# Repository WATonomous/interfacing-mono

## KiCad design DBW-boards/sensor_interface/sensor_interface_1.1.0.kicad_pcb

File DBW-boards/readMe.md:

# DBW Boards
- This folder contaisn schematics, pcb layouts, as well as component lists + where to order for the DBW boards for Watonomous's VP division.
- There are 4 boards to be assembled/fabricated off of these. 
##Boards
- Control (Brake)
- Can Gateway
- 2 Sensor boards, one for throttle and one for steering

### Each board is a Kicad project, simply download this repo and open them in Kicad.

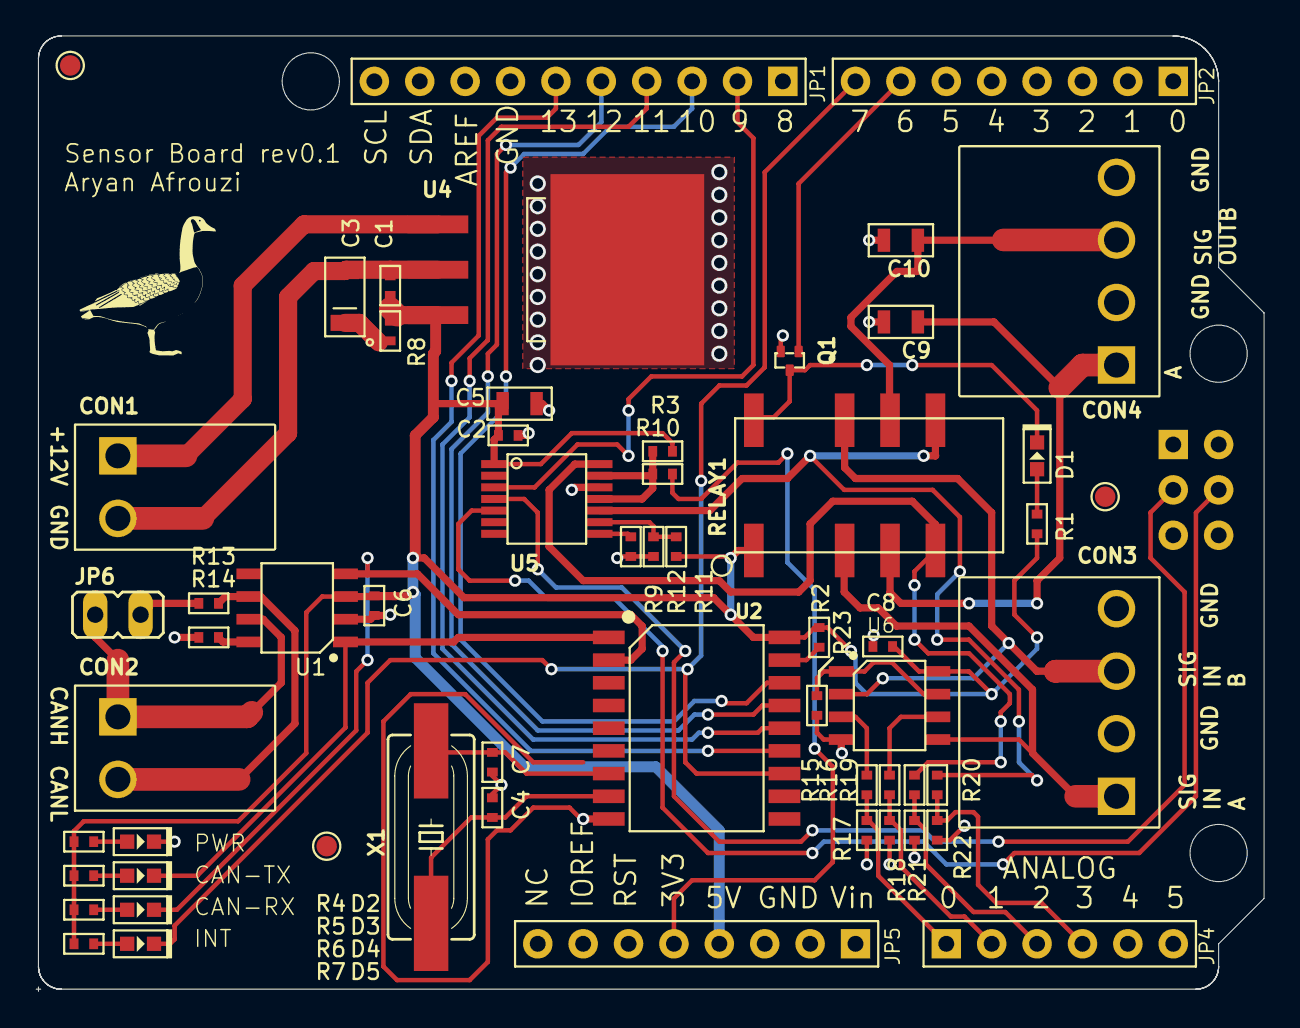
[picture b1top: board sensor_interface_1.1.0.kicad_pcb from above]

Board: 2 copper layers, 68.6 x 53.3 mm, 60 parts (0 on the bottom side), 45 nets.

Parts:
C1, C2, C6, C8: .1u; C0402
C3: 33u; CP1206
C4, C7: 22p; C0402
C5, C9, C10: 10u; C0805
CON1, CON2: CON23.5MM; PHOENIX_2_45
CON3, CON4: PHOENIX_4_45
D1, D4: Red; LED0603
D2, D3: Green; LED0603
D5: Blue; LED0603
JP1: ARDUINO_JP1
JP2: ARDUINO_JP2
JP3: ARDUINO_JP3
JP4: ARDUINO_JP4
JP5: ARDUINO_JP5
JP6: JP1
Q1: RE1C002UN; EMT3F
R1, R4, R5, R6, R7: 1k; R0402
R2, R9, R11, R17, R18, R23: 10k; R0402
R3, R15, R16, R19, R20: 0; R0402
R8: .3; R0402
R10, R12, R21, R22: DNP; R0402
R13: 120; R0402
R14: 47k; R0402
RELAY1: RELAY_DPDT; KEMET_EE2
TP1, TP2, TP3: TP_4545
U1: MCP2551; SOIC8-6.0
U2: MCP2515; SOIC18
U4: TL750M; TO-263
U5: MCP4922T; TSSOP-14
U6: SN74CBT3306CD; SOIC-8
U$1: POLYSYNC_STEERING_BOT
X1: 16MHz; HC49UP

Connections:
+3V3: JP5.22, R10.P$1
+5V: C1.P$1, C2.P$1, C5.P$1, C6.P$1, C8.P$1, JP5.23, R1.P$2, R2.P$1, R3.P$1, R4.P$2, R5.P$2, R6.P$2, R7.P$2, R8.P$1, R11.P$1, RELAY1.P$1, U1.3, U2.18, U4.P$3, U5.P$1, U6.8
ADC0: JP4.27, R15.P$2, R17.P$1
ADC1: JP4.28, R16.P$2, R18.P$1
ADC2: JP4.29, R19.P$2, R21.P$1
ADC3: JP4.30, R20.P$2, R22.P$1
CANH: CON2.P$1, JP6.1, U1.7
CANL: CON2.P$2, R13.P$1, U1.6
CS_A: JP1.10, U5.P$3
CS_B: JP1.11, U2.16
GND: C1.P$2, C2.P$2, C3.P$2, C4.P$1, C5.P$2, C6.P$2, C7.P$1, C8.P$2, C9.P$2, C10.P$2, CON1.P$2, CON3.P$2, CON3.P$4, CON4.P$2, CON4.P$4, D2.CATHODE, JP1.15, JP3.36, JP5.24, JP5.25, Q1.P$2, R9.P$2, R12.P$2, R14.P$2, R17.P$2, R18.P$2, R21.P$2, R22.P$2, R23.P$2, U1.2, U2.9, U4.P$2, U4.P$4, U5.P$12, U6.4
INT: D5.CATHODE, JP2.8, U2.12
LDAC: R9.P$1, U5.P$8
MISO_B: JP1.13, U2.15
MOSI_A: JP3.37, U5.P$5
MOSI_B: JP1.12, U2.14
unnamed: D3.ANODE, R5.P$1
unnamed: JP6.2, R13.P$2
unnamed: D1.CATHODE, Q1.P$3, RELAY1.P$12
unnamed: C3.P$1, R8.P$2
unnamed: D4.ANODE, R6.P$1
unnamed: D2.ANODE, R4.P$1
unnamed: R3.P$2, R10.P$2, U5.P$11, U5.P$13
unnamed: D5.ANODE, R7.P$1
unnamed: R14.P$1, U1.8
unnamed: D1.ANODE, R1.P$1
unnamed: R23.P$1, U6.1, U6.7
unnamed: R16.P$1, U6.6
unnamed: R15.P$1, U6.3
unnamed: C7.P$2, U2.7, X1.2
unnamed: C4.P$2, U2.8, X1.1
RST_N: R2.P$2, U2.17
RX_CAN: D4.CATHODE, U1.4, U2.2
SCK_A: JP3.34, U5.P$4
SCK_B: JP1.14, U2.13
SHDN: R11.P$2, R12.P$1, U5.P$9
SIGNAL_INPUT_A: CON3.P$1, RELAY1.P$3, U6.5
SIGNAL_INPUT_B: CON3.P$3, RELAY1.P$10, U6.2
SIGNAL_OUTPUT_A: C9.P$1, CON4.P$1, RELAY1.P$4
SIGNAL_OUTPUT_B: C10.P$1, CON4.P$3, RELAY1.P$9
SPOOF_EN: JP2.7, Q1.P$1
SPOOF_SIGNAL_A: R19.P$1, RELAY1.P$5, U5.P$14
SPOOF_SIGNAL_B: R20.P$1, RELAY1.P$8, U5.P$10
TX_CAN: D3.CATHODE, U1.1, U2.1
V+: CON1.P$1, U4.P$1

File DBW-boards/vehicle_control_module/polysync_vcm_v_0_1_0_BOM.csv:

Polysync Vehicle Control Module v0.1.0,,,,,,,,,
,,,,,,,,,
Quantity,Reference Designator,Description,Mfg,Mfg Part No.,Distributor,Distributor Part No.,Price,Total Price,
1,R8,RES SMD 0.3 OHM 1% 1/6W 0402,Panasonic Electronic Components,ERJ-2BQFR30X,Digikey,P.30AKCT-ND,0.59,0.59,11
5,"R3, R15, R16, R19, R20",RES SMD 0.0OHM JUMPER 1/10W 0402,Panasonic Electronic Components,ERJ-2GE0R00X,Digikey,P0.0JCT-ND,0.1,0.5,
8,"R2, R9, R11, R17, R18, R23, R24, R25",RES SMD 10K OHM 1% 1/10W 0402,Panasonic Electronic Components,ERJ-2RKF1002X,Digikey,P10.0KLCT-ND,0.1,0.8,13
1,R13,RES SMD 120 OHM 1% 1/10W 0402,Panasonic Electronic Components,ERJ-2RKF1200X,Digikey,P120LCT-ND,0.1,0.1,27
6,"R1, R4, R5, R6, R7, R103",RES SMD 1K OHM 1% 1/10W 0402,Panasonic Electronic Components,ERJ-2RKF1001X,Digikey,P1.00KLCT-ND,0.1,0.6,13
1,R14,RES SMD 47K OHM 1% 1/10W 0402,Panasonic Electronic Components,ERJ-2RKF4702X,Digikey,P47.0KLCT-ND,0.1,0.1,36
4,"R10, R12, R21, R22",DNP,,,,,,,
4,"C1, C2, C6, C8",0.10µF ±10% 16V Ceramic Capacitor X7R 0402 (1005 Metric),Murata Electronics North America,GRM155R71C104KA88J,Digikey,490-6328-1-ND,0.1,0.4,5
3,"C5, C9, C10",10µF ±10% 10V Ceramic Capacitor X7R 0805 (2012 Metric),Taiyo Yuden,LMK212B7106KG-TD,Digikey,587-2668-1-ND,0.28,0.84,4/6???
2,"C4, C7","22pF ±5% 50V Ceramic Capacitor C0G, NP0 0402 (1005 Metric)",Murata Electronics North America,GRM1555C1H220JA01J,Digikey,490-11382-1-ND,0.1,0.2,2
1,C3,33µF ±10% Molded Tantalum Capacitors 10V 1206 (3216 Metric) 1.7 Ohm,AVX Corporation,TAJA336K010RNJ,Digikey,478-8882-1-ND,0.6,0.6,
6,"D1, D2, D3, D4, D5, D17",Blue 470nm LED Indication - Discrete 3.2V 0603 (1608 Metric),Wurth Electronics Inc,150060BS75000,Digikey,732-4966-1-ND,0.26,1.56,3
1,X1,16MHz ±30ppm Crystal 18pF 40 Ohm -40°C ~ 85°C Surface Mount HC49/US,Abracon LLC,ABLS-16.000MHZ-D-4-T,Digikey,535-13436-1-ND,0.24,0.24,1
2,"Q1, Q10",MOSFET N-CH 20V 0.2A EMT3,Rohm Semiconductor,RE1C002UNTCL,Digikey,RE1C002UNTCLCT-ND,0.2,0.4,
1,U2,CAN Controller CAN 2.0 SPI Interface 18-SOIC,Microchip Technology,MCP2515-I/SO,Digikey,MCP2515-I/SO-ND,1.82,1.82,2
1,U1,1/1 Transceiver Half CAN 8-SOIC,Microchip Technology,MCP2551-I/SN,Digikey,MCP2551-I/SN-ND,1.02,1.02,1
1,U5,12 Bit Digital to Analog Converter 2 14-TSSOP,Microchip Technology,MCP4922T-E/ST,Digikey,MCP4922T-E/STCT-ND,2.62,2.62,
1,U4,Linear Voltage Regulator IC Positive Fixed 1 Output 5V 750mA DDPAK/TO-263-3,Texas Instruments,TL750M05CKTTR,Digikey,296-20776-1-ND,1.47,1.47,4
1,U6,IC SWITCH BUS DUAL FET 8-SOIC,Texas Instruments,SN74CBT3306CDR,Digikey,296-19215-1-ND,0.6,0.6,1
2,"RELAY1, RELAY2",General Purpose Relay DPDT (2 Form C) Surface Mount,Kemet,EE2-5NU-L,Digikey,399-11017-1-ND,1.91,3.82,
1,JP1,"10 Positions Header, Unshrouded Connector 0.100"" (2.54mm) Through Hole Gold or Gold, GXT™",Amphenol FCI,68002-210HLF,Digikey,609-3301-ND,0.44,0.44,yes
2,"JP2, JP5","8 Positions Header, Unshrouded Connector 0.100"" (2.54mm) Through Hole Gold or Gold, GXT™",Amphenol FCI,68000-208HLF,Digikey,609-3257-ND,0.43,0.86,yes
1,JP3,"6 Position Receptacle Connector 0.100"" (2.54mm) Through Hole Gold",Amphenol FCI,68683-303LF,Digikey,609-3582-ND,1.61,1.61,yes
1,JP4,"6 Positions Header, Unshrouded Connector 0.100"" (2.54mm) Through Hole Gold or Gold, GXT™",Amphenol FCI,68000-206HLF,Digikey,609-3256-ND,0.32,0.32,yes
1,JP6,"2 Positions Header, Unshrouded Connector 0.100"" (2.54mm) Through Hole Gold or Gold, GXT™",Amphenol FCI,77311-118-02LF,Digikey,609-4434-ND,0.18,0.18,yes
2,"CON1, CON2","2 Position Wire to Board Terminal Block 45° (135°) Angle with Board 0.138"" (3.50mm) Through Hole",Phoenix Contact,1988956,Digikey,277-1779-ND,0.41,0.82,
2,"CON3, CON4","4 Position Wire to Board Terminal Block 45° (135°) Angle with Board 0.138"" (3.50mm) Through Hole",Phoenix Contact,1988972,Digikey,277-1781-ND,0.82,1.64,
2,"CON9, CON10",CONN TERM BLOCK 45DEG 3POS 3.5MM,Phoenix Contact,1988969,Digikey,277-1780-ND,0.65,1.3,
1,For JP6,"2 (1 x 2) Position Shunt Connector White Open Top 0.100"" (2.54mm) Gold or Gold, GXT™",Amphenol FCI,68786-102LF,Digikey,609-3121-ND,0.19,0.19,
Total,,,,,,,,$25.64,

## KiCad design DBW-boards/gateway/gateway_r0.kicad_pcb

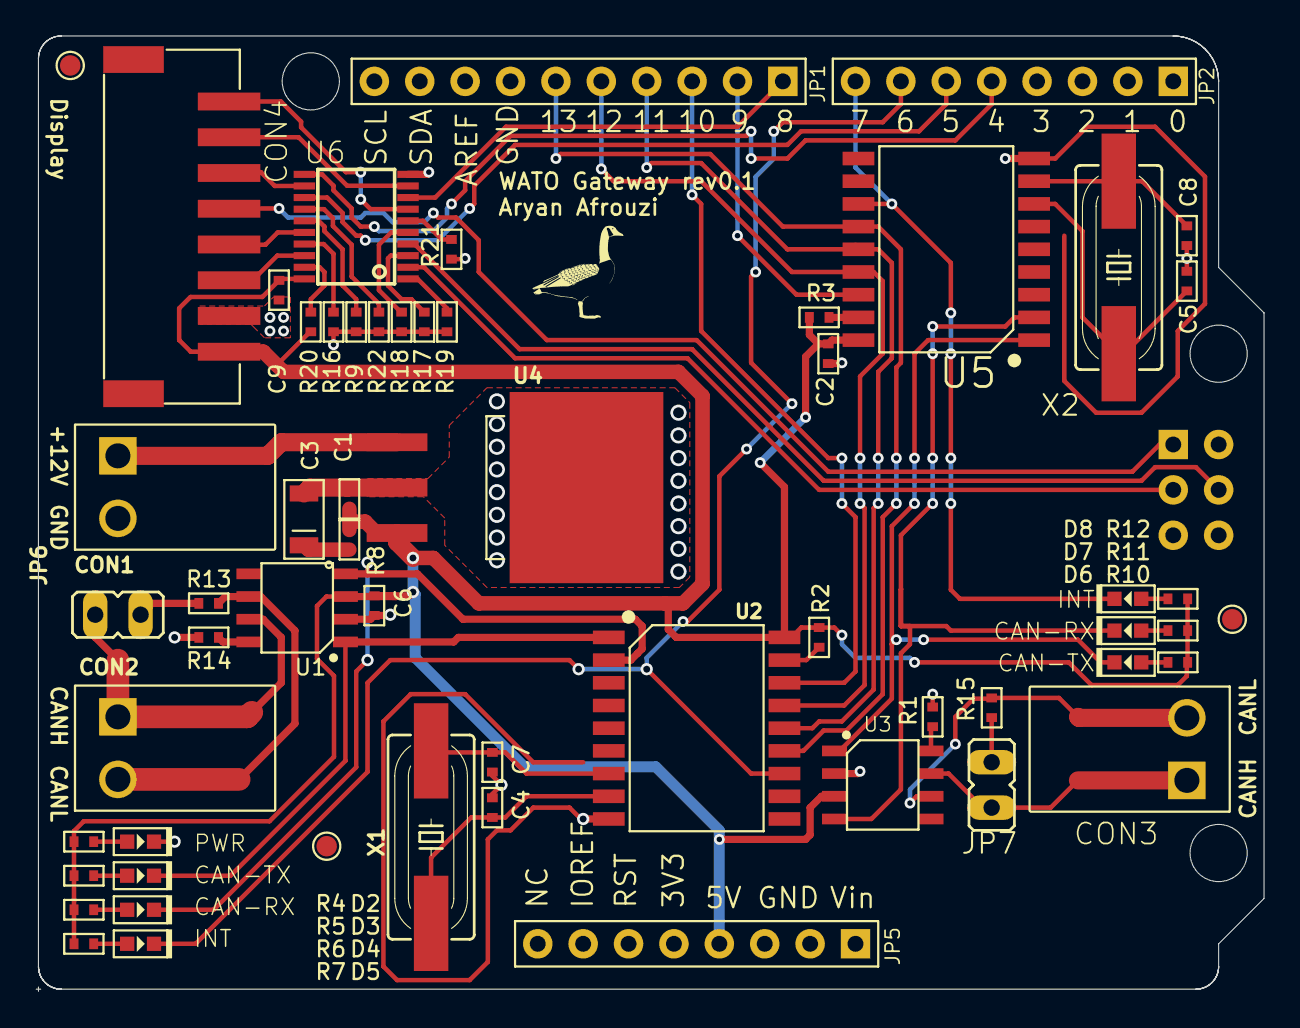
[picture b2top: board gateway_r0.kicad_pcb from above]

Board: 2 copper layers, 68.6 x 53.3 mm, 59 parts (0 on the bottom side), 55 nets.

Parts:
C1, C2, C6, C9: .1u; C0402
C3: 33u; CP1206
C4, C5, C7, C8: 22p; C0402
CON1, CON2, CON3: CON23.5MM; PHOENIX_2_45
CON4: CON8; PH-8-SM
D2, D3, D6: Green; LED0603
D4, D7: Red; LED0603
D5, D8: Blue; LED0603
JP1: ARDUINO_JP1
JP2: ARDUINO_JP2
JP3: ARDUINO_JP3
JP5: ARDUINO_JP5
JP6, JP7: JP1
R1, R14: 47k; R0402
R2, R3, R9, R16, R17, R18, R19, R20, R21, R22: 10k; R0402
R4, R5, R6, R7, R10, R11, R12: 1k; R0402
R8: .3; R0402
R13, R15: 120; R0402
TP1, TP2, TP3: TP_4545
U1, U3: MCP2551; SOIC8-6.0
U2, U5: MCP2515; SOIC18
U4: TL750M; TO-263
U6: 74241PW; PW_R-PDSO-G20
X1, X2: 16MHz; HC49UP

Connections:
164_CS: JP2.5, U6.11
165_~CS: JP2.6, U6.13
+5V: C1.P$1, C2.P$1, C6.P$1, C9.P$1, CON4.P$1, JP5.23, R2.P$1, R3.P$1, R4.P$2, R5.P$2, R6.P$2, R7.P$2, R8.P$1, R10.P$2, R11.P$2, R12.P$2, R20.P$1, U1.3, U2.18, U3.3, U4.P$3, U5.18, U6.20
CANH_0: CON3.P$1, JP7.1, U3.7
CANH_1: CON2.P$1, JP6.1, U1.7
CANL_0: CON3.P$2, R15.P$1, U3.6
CANL_1: CON2.P$2, R13.P$1, U1.6
CS_0: JP1.10, U5.16
CS_1: JP1.11, U2.16
GND: C1.P$2, C2.P$2, C3.P$2, C4.P$1, C5.P$1, C6.P$2, C7.P$1, C8.P$1, C9.P$2, CON1.P$2, CON4.P$2, D2.CATHODE, JP1.15, JP3.36, JP5.24, JP5.25, R1.P$2, R9.P$2, R14.P$2, R16.P$2, R17.P$2, R18.P$2, R19.P$2, R21.P$2, R22.P$2, U1.2, U2.9, U3.2, U4.P$2, U4.P$4, U5.9, U6.10
INT_0: D8.CATHODE, JP2.8, U5.12
INT_1: D5.CATHODE, JP2.7, U2.12
LCD_~CS: JP1.9, U6.8
MISO_A: CON4.P$5, JP3.33
MISO_B: JP1.13, U2.15, U5.15
MOSI_A: JP3.37, U6.4
MOSI_B: JP1.12, U2.14, U5.14
unnamed: D3.ANODE, R5.P$1
unnamed: JP6.2, R13.P$2
unnamed: C5.P$2, U5.7, X2.2
unnamed: C3.P$1, R8.P$2
unnamed: D4.ANODE, R6.P$1
unnamed: D2.ANODE, R4.P$1
unnamed: C8.P$2, U5.8, X2.1
unnamed: D5.ANODE, R7.P$1
unnamed: R14.P$1, U1.8
unnamed: R1.P$1, U3.8
unnamed: CON4.P$3, U6.18
unnamed: D6.ANODE, R10.P$1
unnamed: D7.ANODE, R11.P$1
unnamed: D8.ANODE, R12.P$1
unnamed: JP7.2, R15.P$2
unnamed: C7.P$2, U2.7, X1.2
unnamed: C4.P$2, U2.8, X1.1
unnamed: CON4.P$4, U6.16
unnamed: R21.P$1, U6.6
unnamed: CON4.P$6, U6.12
unnamed: CON4.P$7, U6.9
unnamed: CON4.P$8, U6.7
unnamed: R9.P$1, U6.15
unnamed: R16.P$1, U6.17
unnamed: R17.P$1, U6.3
unnamed: R18.P$1, U6.5
unnamed: R19.P$1, U6.1
unnamed: R20.P$2, U6.19
unnamed: R22.P$1, U6.14
RST_N: R2.P$2, U2.17
RST_N1: R3.P$2, U5.17
RX_CAN_0: D7.CATHODE, U3.4, U5.2
RX_CAN_1: D4.CATHODE, U1.4, U2.2
SCK_A: JP3.34, U6.2
SCK_B: JP1.14, U2.13, U5.13
TX_CAN_0: D6.CATHODE, U3.1, U5.1
TX_CAN_1: D3.CATHODE, U1.1, U2.1
V+: CON1.P$1, U4.P$1

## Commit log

2024-08-24 init
2024-08-24 boilerplate mux
2024-08-31 staging
2024-09-14 embedded oscc and joystick commander to repo. changes to arbiter too
2024-09-14 Added oscc-joystick-commander as part of the main repository
2024-09-16 Adding Board files, read me to mono-repo
2024-10-14 test publishers
2025-01-09 stashing changes from like october lol
